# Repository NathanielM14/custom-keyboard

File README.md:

custom-keyboard

**Personal Project Description**:

Currently desigining a 67-key matrix compact keyboard pcb, which will be paired with a custom chassis which will be designed using Fusion 360 to house the PCB. The board has hot-swap capable for the Geteron KS-33 Low Profile 2.0 Mechanical Switches.

1. Schematic

3. PCB

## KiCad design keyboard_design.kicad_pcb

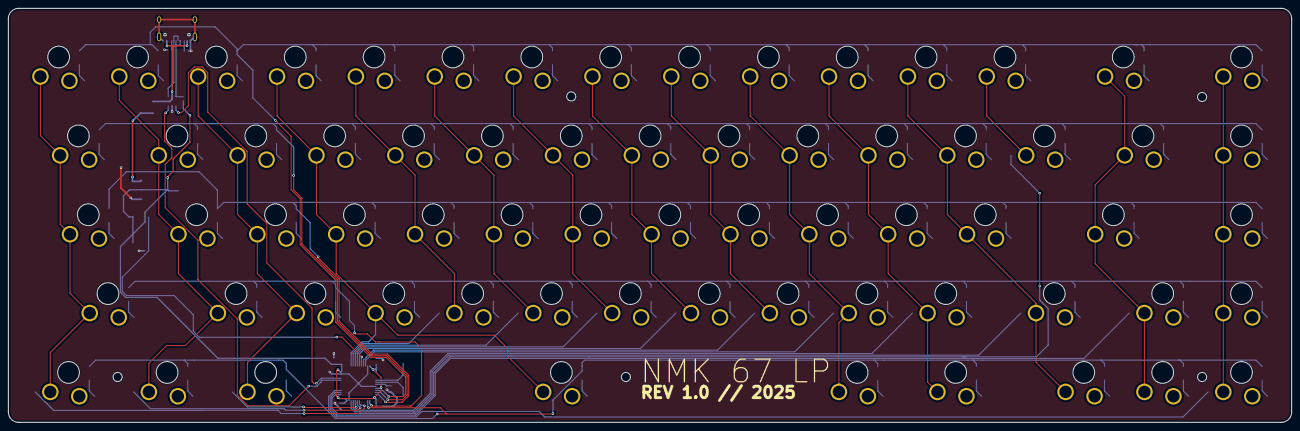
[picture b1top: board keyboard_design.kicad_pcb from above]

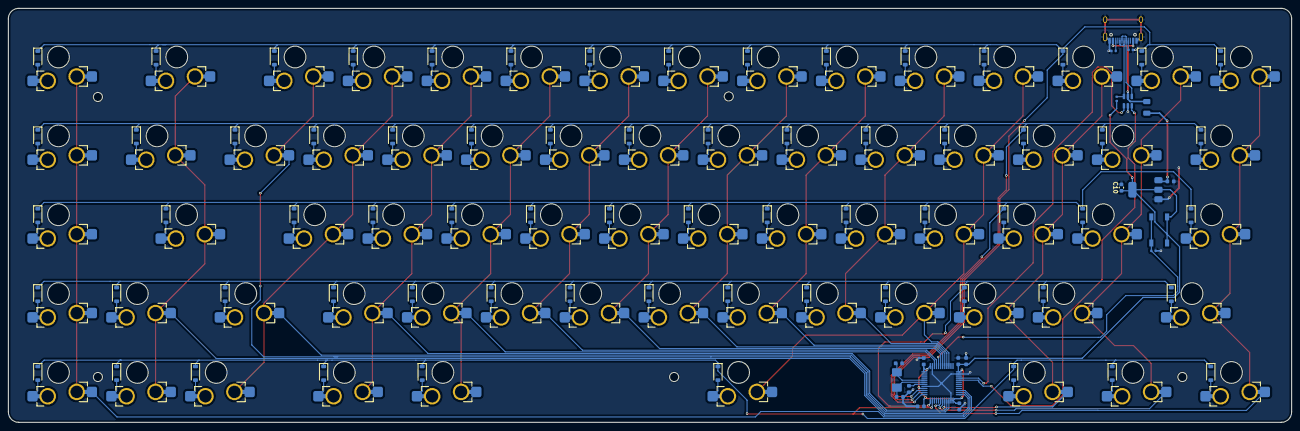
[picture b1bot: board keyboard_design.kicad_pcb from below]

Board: 2 copper layers, 310.0 x 100.0 mm, 155 parts (88 on the bottom side), 101 nets.

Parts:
C1: 10u; C_0603_1608Metric
C2, C3, C4, C5, C8: 100n; C_0603_1608Metric
C6, C7: 33p; C_0603_1608Metric
C9, C10: 22u; C_0603_1608Metric
D1, D2, D3, D4, D5, D6, D7, D8, D9, D10, D11, D12, D13, D14, D15, D16, D17, D18, D19, D20, D21, D22, D23, D24, D25, D26, D27, D28, D29, D30, D31, D32, D33, D34, D35, D36, D37, D38, D39, D40, D41, D42, D43, D44, D45, D46, D47, D48, D49, D50, D51, D52, D53, D54, D55, D56, D57, D58, D59, D60, D61, D62, D63, D64, D65, D66, D67: Diode; D_SOD-123
F1: 500mA; Fuse_1206_3216Metric
J1: USB_C_Receptacle_USB2.0_14P; USB_C_Receptacle_HRO_TYPE-C-31-M-12
R1: 10K; R_0402_1005Metric
R2, R3: 5.1k; R_0402_1005Metric
R4: 1.5k; R_0402_1005Metric
SW1, SW2, SW3, SW4, SW5, SW6, SW7, SW8, SW9, SW10, SW11, SW12, SW13, SW14, SW15, SW16, SW17, SW18, SW19, SW20, SW21, SW22, SW23, SW24, SW25, SW26, SW27, SW28, SW29, SW30, SW31, SW32, SW33, SW34, SW35, SW36, SW37, SW38, SW39, SW40, SW41, SW42, SW43, SW44, SW45, SW46, SW47, SW48, SW49, SW50, SW51, SW52, SW53, SW54, SW55, SW56, SW57, SW58, SW59, SW60, SW61, SW62, SW63, SW64, SW65, SW66, SW67: Keyswitch; SW_Gateron_LowProfile_HotSwap_PTH
SWT1: SW_Push; SW_SPST_TL3342
U1: STM32F103C8T6; LQFP-48_7x7mm_P0.5mm
U2: USBLC6-2SC6; SOT-23-6
U3: AMS1117-3.3; SOT-223-3_TabPin2
Y1: 8MHz; Crystal_SMD_5032-2Pin_5.0x3.2mm

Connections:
+3.3V: C1.1, C2.1, C3.1, C4.1, C5.1, C10.1, R4.1, SWT1.1, U1.1 (VBAT), U1.9 (VDDA), U1.24 (VDD), U1.36 (VDD), U1.48 (VDD), U3.2 (VO)
+5V: C9.1, F1.2, U3.3 (VI)
/NRST: C8.1, U1.7 (NRST)
Column 0: SW1.1, SW16.1, SW31.1, SW45.1, SW59.1, U1.18 (PB0)
Column 1: SW2.1, SW17.1, SW32.1, SW46.1, SW60.1, U1.19 (PB1)
Column 2: SW3.1, SW18.1, SW33.1, SW47.1, SW61.1, U1.20 (PB2)
Column 3: SW4.1, SW19.1, SW34.1, SW48.1, SW62.1, U1.39 (PB3)
Column 4: SW5.1, SW20.1, SW35.1, SW49.1, U1.40 (PB4)
Column 5: SW6.1, SW21.1, SW36.1, SW50.1, U1.41 (PB5)
Column 6: SW7.1, SW22.1, SW37.1, SW51.1, U1.42 (PB6)
Column 7: SW8.1, SW23.1, SW38.1, SW52.1, U1.43 (PB7)
Column 8: SW9.1, SW24.1, SW39.1, SW53.1, U1.45 (PB8)
Column 9: SW10.1, SW25.1, SW40.1, SW54.1, SW63.1, U1.46 (PB9)
Column 10: SW11.1, SW26.1, SW41.1, SW55.1, SW64.1, U1.21 (PB10)
Column 11: SW12.1, SW27.1, SW42.1, SW56.1, SW65.1, U1.22 (PB11)
Column 12: SW13.1, SW28.1, U1.25 (PB12)
Column 13: SW14.1, SW29.1, SW43.1, SW57.1, SW66.1, U1.26 (PB13)
Column 14: SW15.1, SW30.1, SW44.1, SW58.1, SW67.1, U1.27 (PB14)
DM: J1.A7 (D-), J1.B7 (D-), U2.4 (I/O2)
DP: J1.A6 (D+), J1.B6 (D+), R4.2, U2.6 (I/O1)
GND: C1.2, C2.2, C3.2, C4.2, C5.2, C6.2, C7.2, C8.2, C9.2, C10.2, J1.A1 (GND), J1.A12 (GND), J1.B1 (GND), J1.B12 (GND), J1.S1 (SHIELD), R1.2, R2.2, R3.1, U1.8 (VSSA), U1.23 (VSS), U1.35 (VSS), U1.47 (VSS), U2.2 (GND), U3.1 (GND)
MCU_DM: U1.32 (PA11), U2.3 (I/O2)
MCU_DP: U1.33 (PA12), U2.1 (I/O1)
unnamed: D1.2 (A), SW1.2
unnamed: D2.2 (A), SW2.2
unnamed: D3.2 (A), SW3.2
unnamed: D4.2 (A), SW4.2
unnamed: D5.2 (A), SW5.2
unnamed: D6.2 (A), SW6.2
unnamed: D7.2 (A), SW7.2
unnamed: D8.2 (A), SW8.2
unnamed: D9.2 (A), SW9.2
unnamed: D10.2 (A), SW10.2
unnamed: D11.2 (A), SW11.2
unnamed: D12.2 (A), SW12.2
unnamed: D13.2 (A), SW13.2
unnamed: D14.2 (A), SW14.2
unnamed: D15.2 (A), SW15.2
unnamed: D16.2 (A), SW16.2
unnamed: D17.2 (A), SW17.2
unnamed: D18.2 (A), SW18.2
unnamed: D19.2 (A), SW19.2
unnamed: D20.2 (A), SW20.2
unnamed: D21.2 (A), SW21.2
unnamed: D22.2 (A), SW22.2
unnamed: D23.2 (A), SW23.2
unnamed: D24.2 (A), SW24.2
unnamed: D25.2 (A), SW25.2
unnamed: D26.2 (A), SW26.2
unnamed: D27.2 (A), SW27.2
unnamed: D28.2 (A), SW28.2
unnamed: D29.2 (A), SW29.2
unnamed: D30.2 (A), SW30.2
unnamed: D31.2 (A), SW31.2
unnamed: D32.2 (A), SW32.2
unnamed: D33.2 (A), SW33.2
unnamed: D34.2 (A), SW34.2
unnamed: D35.2 (A), SW35.2
unnamed: D36.2 (A), SW36.2
unnamed: D37.2 (A), SW37.2
unnamed: D38.2 (A), SW38.2
unnamed: D39.2 (A), SW39.2
unnamed: D40.2 (A), SW40.2
unnamed: D41.2 (A), SW41.2
unnamed: D42.2 (A), SW42.2
unnamed: D43.2 (A), SW43.2
unnamed: D44.2 (A), SW44.2
unnamed: D45.2 (A), SW45.2
unnamed: D46.2 (A), SW46.2
unnamed: D47.2 (A), SW47.2
unnamed: D48.2 (A), SW48.2
unnamed: D49.2 (A), SW49.2
unnamed: D50.2 (A), SW50.2
unnamed: D51.2 (A), SW51.2
unnamed: D52.2 (A), SW52.2
unnamed: D53.2 (A), SW53.2
unnamed: D54.2 (A), SW54.2
unnamed: D55.2 (A), SW55.2
unnamed: D56.2 (A), SW56.2
unnamed: D57.2 (A), SW57.2
unnamed: D58.2 (A), SW58.2
unnamed: D59.2 (A), SW59.2
unnamed: D60.2 (A), SW60.2
unnamed: D61.2 (A), SW61.2
unnamed: D62.2 (A), SW62.2
unnamed: D63.2 (A), SW63.2
unnamed: D64.2 (A), SW64.2
unnamed: D65.2 (A), SW65.2
unnamed: D66.2 (A), SW66.2
unnamed: D67.2 (A), SW67.2
unnamed: J1.A5 (CC1), R2.1
unnamed: J1.B5 (CC2), R3.2
unnamed: R1.1, SWT1.2, U1.44 (BOOT0)
OSC_IN: C6.1, U1.5 (PD0), Y1.1
OSC_OUT: C7.1, U1.6 (PD1), Y1.2
Row 0: D1.1 (K), D2.1 (K), D3.1 (K), D4.1 (K), D5.1 (K), D6.1 (K), D7.1 (K), D8.1 (K), D9.1 (K), D10.1 (K), D11.1 (K), D12.1 (K), D13.1 (K), D14.1 (K), D15.1 (K), U1.10 (PA0)
Row 1: D16.1 (K), D17.1 (K), D18.1 (K), D19.1 (K), D20.1 (K), D21.1 (K), D22.1 (K), D23.1 (K), D24.1 (K), D25.1 (K), D26.1 (K), D27.1 (K), D28.1 (K), D29.1 (K), D30.1 (K), U1.11 (PA1)
Row 2: D31.1 (K), D32.1 (K), D33.1 (K), D34.1 (K), D35.1 (K), D36.1 (K), D37.1 (K), D38.1 (K), D39.1 (K), D40.1 (K), D41.1 (K), D42.1 (K), D43.1 (K), D44.1 (K), U1.12 (PA2)
Row 3: D45.1 (K), D46.1 (K), D47.1 (K), D48.1 (K), D49.1 (K), D50.1 (K), D51.1 (K), D52.1 (K), D53.1 (K), D54.1 (K), D55.1 (K), D56.1 (K), D57.1 (K), D58.1 (K), U1.13 (PA3)
Row 4: D59.1 (K), D60.1 (K), D61.1 (K), D62.1 (K), D63.1 (K), D64.1 (K), D65.1 (K), D66.1 (K), D67.1 (K), U1.14 (PA4)
VBUS: F1.1, J1.A4 (VBUS), J1.A9 (VBUS), J1.B4 (VBUS), J1.B9 (VBUS), U2.5 (VBUS)

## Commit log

2025-09-13 Create a
2025-09-13 Create temp
2025-09-13 Rename Screenshot 2025-09-13 152458.png to pcb_design.png
